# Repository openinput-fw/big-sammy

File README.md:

# big-sammy

Open source wired mouse hardware.

Please see the [documentation](https://big-sammy.readthedocs.io/en/latest) for more information.

## Specifications
- 8 kHz sampling rate support
- Zero latency switch debounce
- Onboard configuration memory
- 2 main mouse buttons (satellite* configuration for both)
- 2 side buttons (symmetric to allow easy left/right handedness)
- encoder + wheel button (satellite* configuration)
- RGB Led

`*meaning, a separate board from the core with the controller and sensor`

## Firmware

*big-sammy* is meant to run on [openinput](https://github.com/openinput-fw/openinput).

## License

This hardware is licensed under the [CERN-OHL-P v2](LICENSE) license.

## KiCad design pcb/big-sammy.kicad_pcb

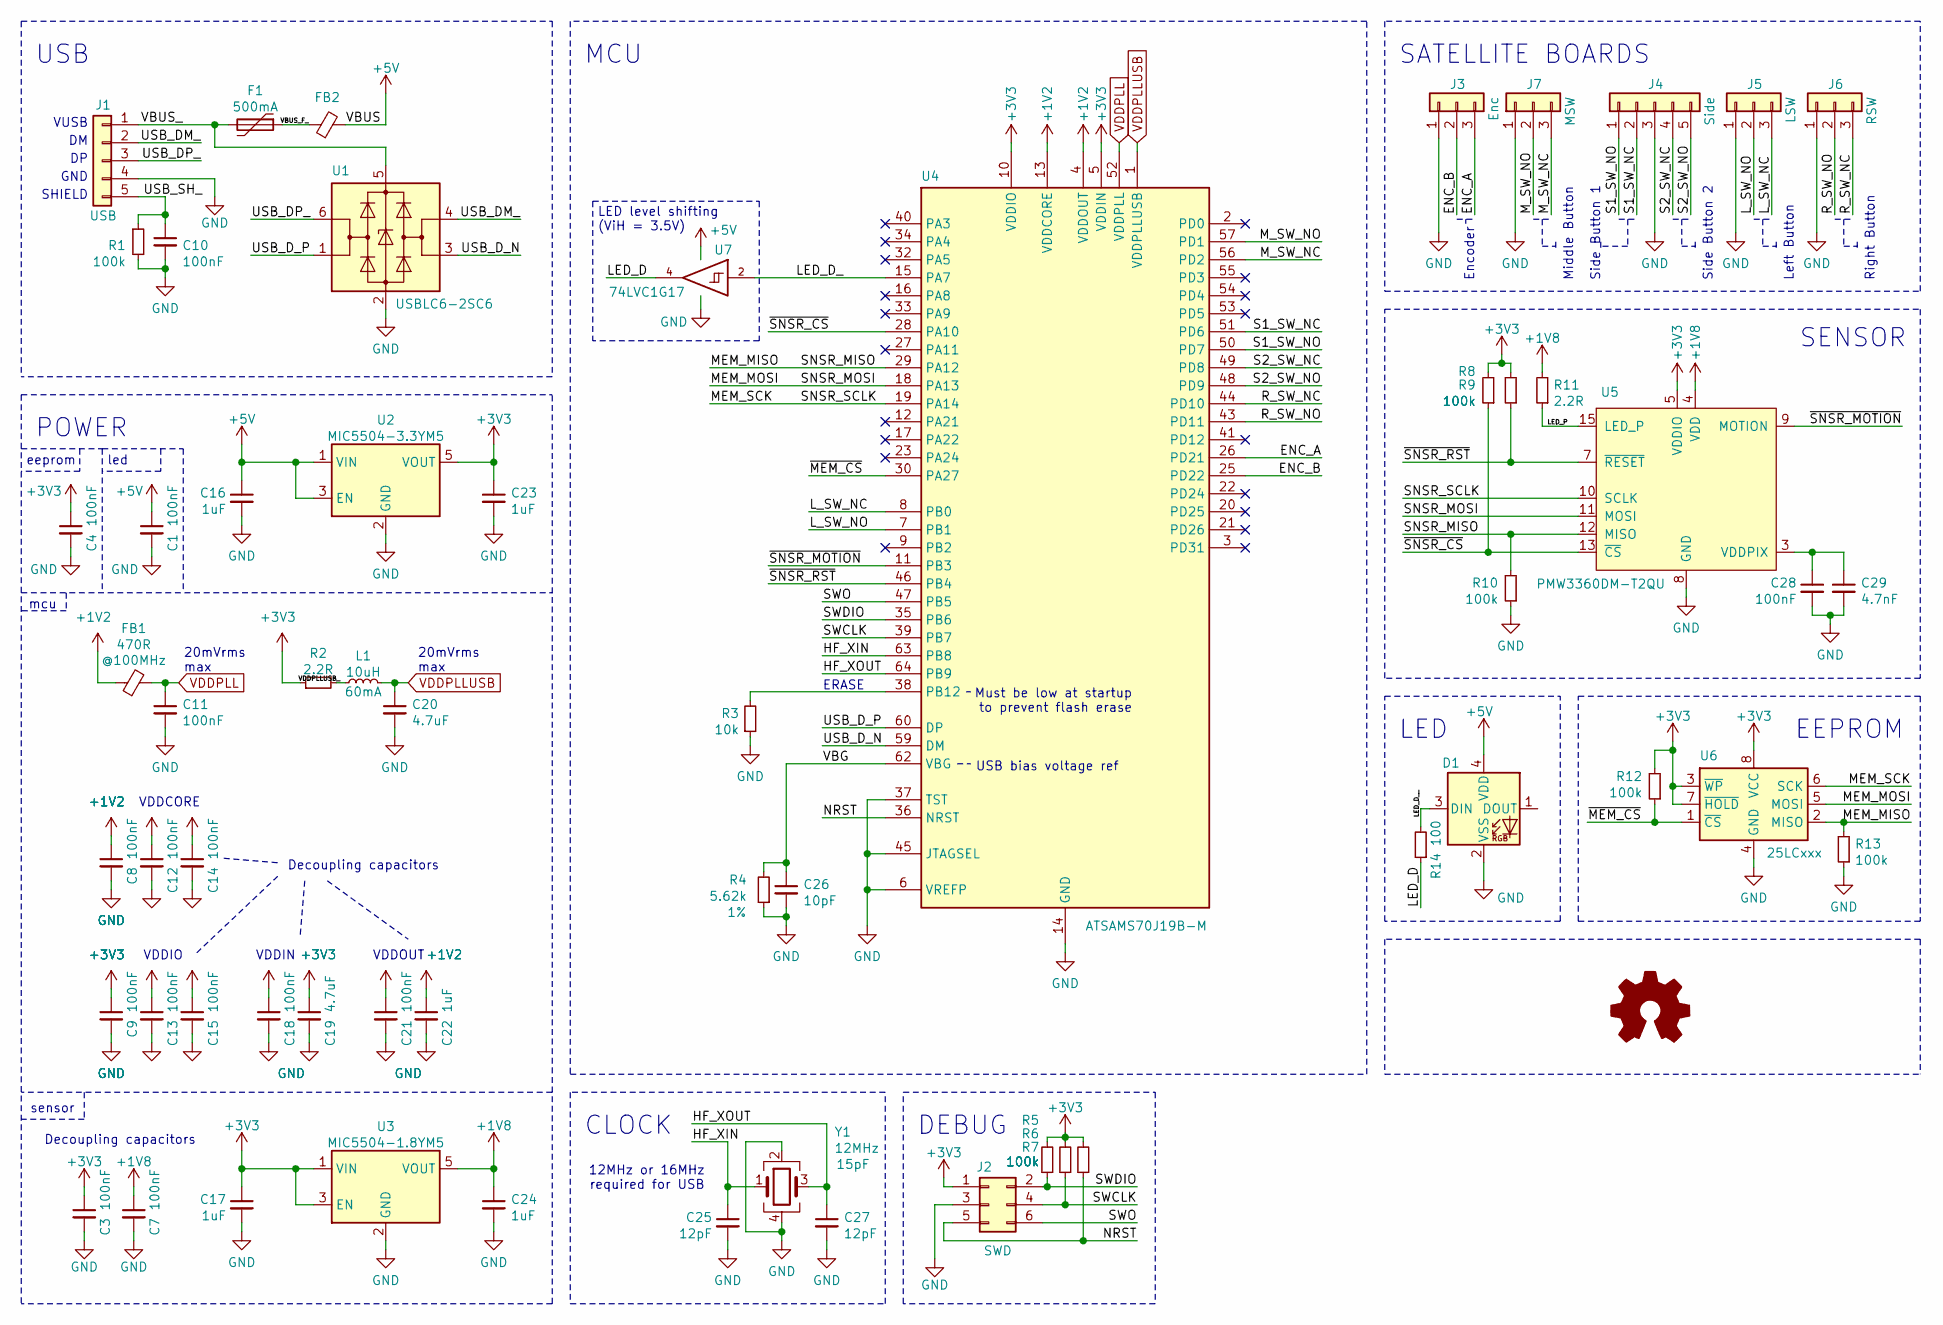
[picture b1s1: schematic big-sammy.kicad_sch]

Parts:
C1, C3, C4, C7, C8, C9, C10, C11, C12, C13, C14, C15, C18, C21, C28: 100nF; C_0402_1005Metric
C16, C17, C22, C23, C24: 1uF; C_0603_1608Metric
C19, C20: 4.7uF; C_0603_1608Metric
C25, C27: 12pF; C_0402_1005Metric
C26: 10pF; C_0402_1005Metric
C29: 4.7nF; C_0402_1005Metric
D1: ws2812-2020
F1: 500mA; Fuse_0603_1608Metric_Castellated
FB1: 470R; L_0402_1005Metric
FB2: L_0402_1005Metric
J1: USB; JST_PH_B5B-PH-K_1x05_P2.00mm_Vertical
J2: SWD; Tag-Connect_TC2030-IDC-NL_2x03_P1.27mm_Vertical
J3: Enc; JST_SH_BM03B-SRSS-TB_1x03-1MP_P1.00mm_Vertical
J4: Side; JST_SH_BM05B-SRSS-TB_1x05-1MP_P1.00mm_Vertical
J5: LSW; JST_SH_BM03B-SRSS-TB_1x03-1MP_P1.00mm_Vertical
J6: RSW; JST_SH_BM03B-SRSS-TB_1x03-1MP_P1.00mm_Vertical
J7: MSW; JST_SH_BM03B-SRSS-TB_1x03-1MP_P1.00mm_Vertical
L1: 10uH; L_0402_1005Metric
R1, R5, R6, R7, R8, R9, R10, R12, R13: 100k; R_0402_1005Metric
R2, R11: 2.2R; R_0402_1005Metric
R3: 10k; R_0402_1005Metric
R4: 5.62k; R_0402_1005Metric; Tolerance 1%
R14: 100; R_0402_1005Metric
U1: USBLC6-2SC6; SOT-23-6
U2: MIC5504-3.3YM5; SOT-23-5
U3: MIC5504-1.8YM5; SOT-23-5
U4: ATSAMS70J19B-M; QFN-64-1EP_9x9mm_P0.5mm_EP7.65x7.65mm
U5: PMW3360DM-T2QU; PMW3360
U6: 25LCxxx; DFN-S-8-1EP_6x5mm_P1.27mm
U7: 74LVC1G17; SOT-353_SC-70-5
Y1: 12MHz; Crystal_SMD_3225-4Pin_3.2x2.5mm

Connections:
+1V2: C8.1, C12.1, C14.1, C21.1, C22.1, FB1.1, U4.4 (VDDOUT), U4.13 (VDDCORE), U4.24 (VDDCORE), U4.61 (VDDCORE)
+1V8: C7.1, C24.1, R11.2, U3.5 (VOUT), U5.4 (VDD)
+3V3: C3.1, C4.1, C9.1, C13.1, C15.1, C17.1, C18.1, C19.1, C23.1, J2.1, R2.1, R5.2, R6.2, R7.2, R8.2, R9.2, R12.2, U2.5 (VOUT), U3.1 (VIN), U3.3 (EN), U4.5 (VDDIN), U4.10 (VDDIO), U4.42 (VDDIO), U4.58 (VDDIO), U5.5 (VDDIO), U6.3 (~WP), U6.7 (~HOLD), U6.8 (VCC)
+5V: C1.1, C16.1, D1.4 (VDD), FB2.2, U2.1 (VIN), U2.3 (EN), U7.5 (VCC)
/ENC_A: J3.3, U4.26 (PD21)
/ENC_B: J3.2, U4.25 (PD22)
/HF_XIN: C25.1, U4.63 (PB8), Y1.1
/HF_XOUT: C27.1, U4.64 (PB9), Y1.3
/LED_D: R14.1, U7.4
/LED_D_: U4.15 (PA7), U7.2
/LED_D__: D1.3 (DIN), R14.2
/LED_P: R11.1, U5.15 (LED_P)
/L_SW_NC: J5.3, U4.8 (PB0)
/L_SW_NO: J5.2, U4.7 (PB1)
/MEM_MISO: R10.2, R13.2, U4.29 (PA12), U5.12 (MISO), U6.2 (MISO)
/MEM_MOSI: U4.18 (PA13), U5.11 (MOSI), U6.5 (MOSI)
/MEM_SCK: U4.19 (PA14), U5.10 (SCLK), U6.6 (SCK)
/M_SW_NC: J7.3, U4.56 (PD2)
/M_SW_NO: J7.2, U4.57 (PD1)
/NRST: J2.5, R7.1, U4.36 (NRST)
/R_SW_NC: J6.3, U4.44 (PD10)
/R_SW_NO: J6.2, U4.43 (PD11)
/S1_SW_NC: J4.2, U4.51 (PD6)
/S1_SW_NO: J4.1, U4.50 (PD7)
/S2_SW_NC: J4.4, U4.49 (PD8)
/S2_SW_NO: J4.5, U4.48 (PD9)
/SWCLK: J2.4, R6.1, U4.39 (PB7)
/SWDIO: J2.2, R5.1, U4.35 (PB6)
/SWO: J2.6, U4.47 (PB5)
/USB_DM_: J1.2, U1.4 (I/O2)
/USB_DP_: J1.3, U1.6 (I/O1)
/USB_D_N: U1.3 (I/O2), U4.59 (DM)
/USB_D_P: U1.1 (I/O1), U4.60 (DP)
/USB_SH_: C10.1, J1.5, R1.1
/VBG: C26.1, R4.2, U4.62 (VBG)
/VBUS_: F1.2, J1.1, U1.5 (VBUS)
/VBUS_F_: F1.1, FB2.1
/VDDPLLUSB_: L1.1, R2.2
/~MEM_CS: R12.1, U4.30 (PA27), U6.1 (~CS)
/~SNSR_CS: R8.1, U4.28 (PA10), U5.13 (~CS)
/~SNSR_MOTION: U4.11 (PB3), U5.9 (MOTION)
/~SNSR_RST: R9.1, U4.46 (PB4), U5.7 (~RESET)
GND: C1.2, C3.2, C4.2, C7.2, C8.2, C9.2, C10.2, C11.2, C12.2, C13.2, C14.2, C15.2, C16.2, C17.2, C18.2, C19.2, C20.2, C21.2, C22.2, C23.2, C24.2, C25.2, C26.2, C27.2, C28.2, C29.2, D1.2 (VSS), J1.4, J2.3, J3.1, J4.3, J5.1, J6.1, J7.1, R1.2, R3.1, R4.1, R10.1, R13.1, U1.2 (GND), U2.2 (GND), U3.2 (GND), U4.6 (VREFP), U4.14 (GND), U4.31 (GND), U4.37 (TST), U4.45 (JTAGSEL), U4.65 (GND), U5.8 (GND), U6.4 (GND), U7.3 (GND), Y1.2, Y1.4
unnamed: C28.1, C29.1, U5.3 (VDDPIX)
unnamed: R3.2, U4.38 (PB12)
VDDPLL: C11.1, FB1.2, U4.52 (VDDPLL)
VDDPLLUSB: C20.1, L1.2, U4.1 (VDDPLLUSB)

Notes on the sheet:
Side Button 2
Left Button
DEBUG
USB
20mVrms max
CLOCK
SENSOR
USB bias voltage ref
VDDCORE
SHIELD
Right Button
VUSB
led
MCU
12MHz or 16MHz required for USB
mcu
Decoupling capacitors
Side Button 1
GND
POWER
sensor
Encoder
Middle Button
eeprom
SATELLITE BOARDS
VDDIO
LED
ERASE
LED level shifting (ViH = 3.5V)
VDDIN
Must be low at startup to prevent flash erase
EEPROM
VDDOUT

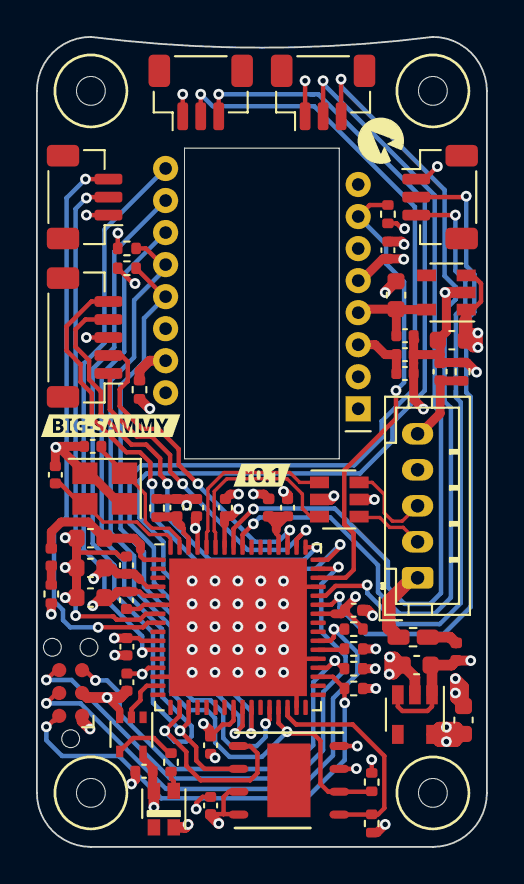
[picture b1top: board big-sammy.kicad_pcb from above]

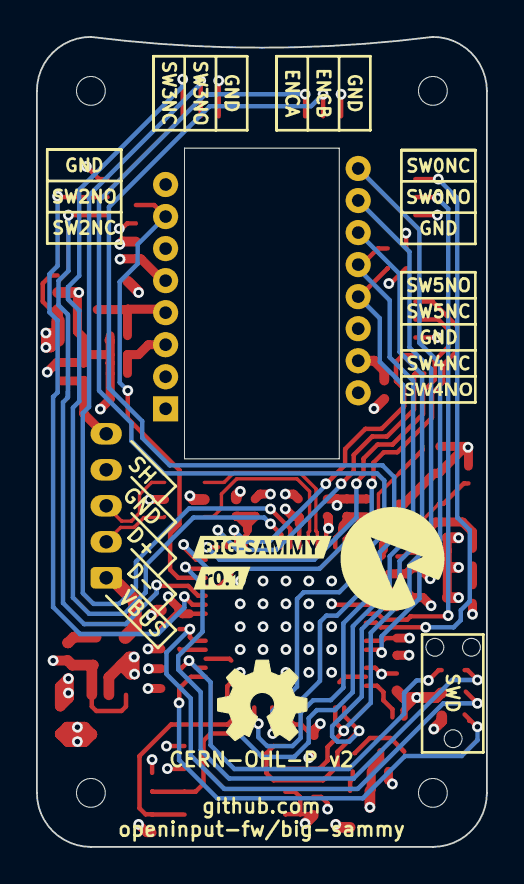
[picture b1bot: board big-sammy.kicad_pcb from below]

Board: 4 copper layers, 25.0 x 45.0 mm, 65 parts (3 on the bottom side), 47 nets.

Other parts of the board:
svg2mod, svg2mod#2, svg2mod#3, svg2mod#4, svg2mod#5: G***; svg2mod

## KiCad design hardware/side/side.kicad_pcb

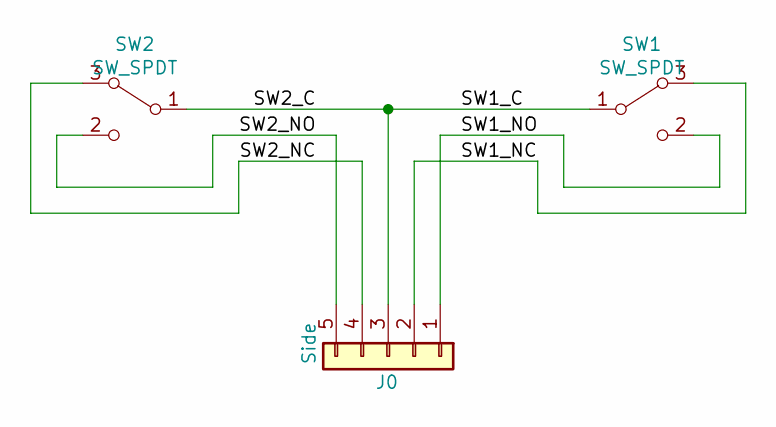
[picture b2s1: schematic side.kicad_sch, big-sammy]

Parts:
J0: Side; PinHeader_1x05_P2.00mm_Vertical
SW1, SW2: SW_SPDT; Generic

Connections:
/SW1_C: J0.3, SW1.1 (B), SW2.1 (B)
/SW1_NC: J0.2, SW1.3 (A)
/SW1_NO: J0.1, SW1.2 (C)
/SW2_NC: J0.4, SW2.3 (A)
/SW2_NO: J0.5, SW2.2 (C)

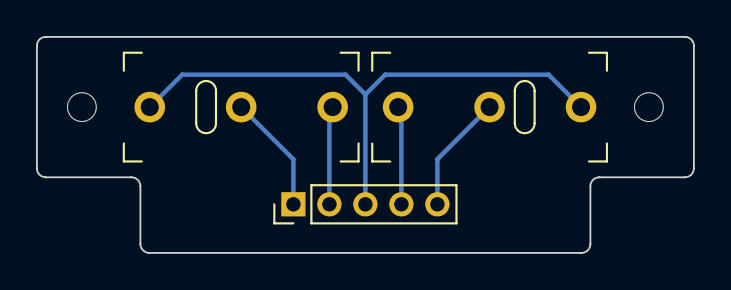
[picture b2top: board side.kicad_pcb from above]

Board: 4 copper layers, 36.5 x 12.0 mm, 3 parts (0 on the bottom side), 5 nets.

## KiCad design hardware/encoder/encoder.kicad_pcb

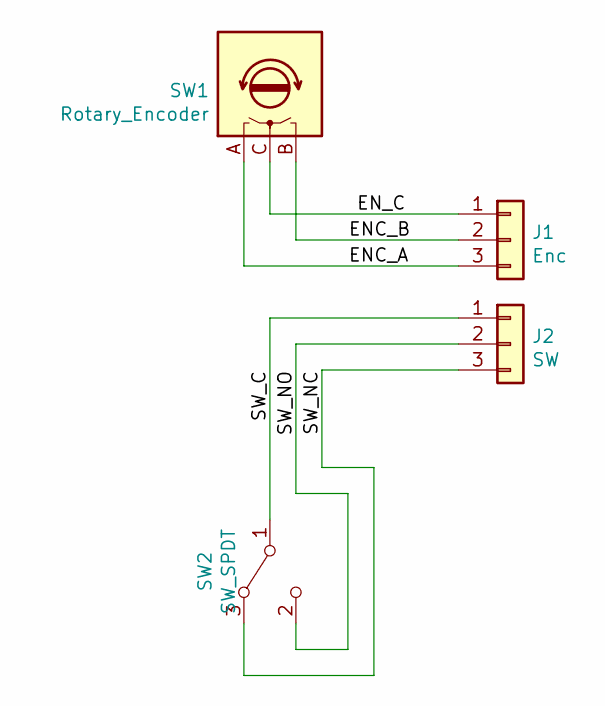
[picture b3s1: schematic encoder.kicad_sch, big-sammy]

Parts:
J1: Enc; PinHeader_1x03_P2.00mm_Vertical
J2: SW; PinHeader_1x03_P2.00mm_Vertical
SW1: Rotary_Encoder; Encoder
SW2: SW_SPDT; Generic

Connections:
/ENC_A: J1.3, SW1.A
/ENC_B: J1.2, SW1.B
/EN_C: J1.1, SW1.C
/SW_C: J2.1, SW2.1 (B)
/SW_NC: J2.3, SW2.3 (A)
/SW_NO: J2.2, SW2.2 (C)

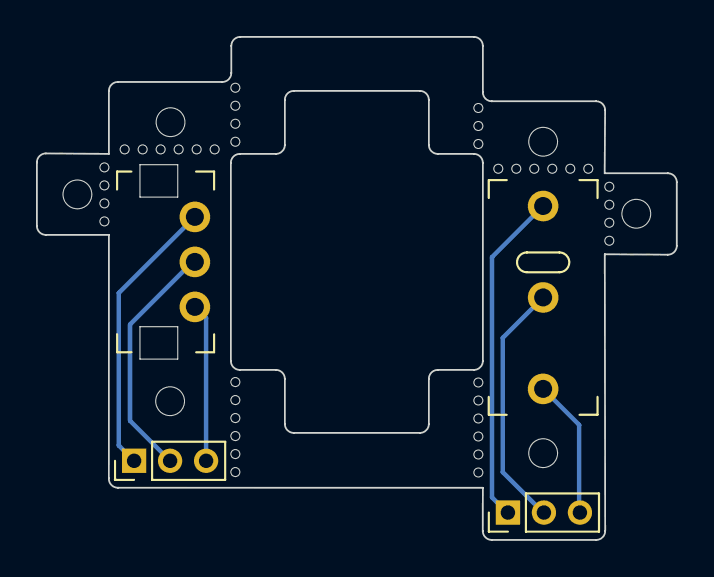
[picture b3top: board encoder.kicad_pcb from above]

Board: 4 copper layers, 35.5 x 27.9 mm, 4 parts (0 on the bottom side), 6 nets.

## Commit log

2021-04-10 license: add CERN-OHL-P v2 license
2021-04-10 readme: add readme
2021-04-10 hardware: add base projects
2021-04-10 readme: clarify mcu selection
2021-04-13 readme: add usb pinout
2021-04-13 kicad: add local libraries
2021-04-13 schematic: implement core board
2021-04-13 schematic: add current repo url
2021-04-13 git: kicad: add kicad lib backups to gitignore
2021-04-13 schematic: implement side boards
2021-04-13 schematic: add missing library table
2021-04-13 schematic: core: add rgb led
2021-04-13 schematic: core: add labels
2021-04-13 readme: add RGB Led to spec list
2021-04-13 schematic: core: fix erase pull down value (internall 100k in parallel)
2021-04-13 name: renamed project
2021-04-13 readme: mention more compatible sensors
2021-04-13 readme: add firmware section
2021-04-13 hardware: add project footprint table
2021-04-13 hardware: fix kicad table links
2021-04-13 schematic: core: changed encoder board pinout
2021-04-13 pcb: encoder: layout
2021-04-13 pcb: side: layout
2021-04-13 pcb: switch: layout
2021-04-20 pcb: core: component positioning
2021-04-21 kicad: libraries
2021-04-21 core: layout
2021-04-22 kicad: add M1.4 mounting hole
2021-04-22 core: finalize layout
2021-04-22 core: document label creation details
2021-04-22 switch: add alternative mounting points
2021-04-22 side: change mounting hardware from m2 to m1.4
2021-04-22 encoder: rework encoder board
2021-04-22 rev: bum rev to r0.1
2021-04-22 repo: update name and references to source
2021-04-22 core: pcb: fixup encoder trace
2021-04-22 readme: add r0.1 render
2021-04-22 core: pcb: fixup SW trace
2021-04-30 pcb: move kicad project, seperate generic boards from repo
2021-04-30 kicad: removed unused libs
2021-06-07 fix #1: typo in link to source
2021-07-02 readme: add peripheral board reference
2021-10-15 assets: move assets to docs/assets
2021-10-15 docs: add initial documentation with sphinx
2021-10-15 assets: oi logo cleanup
2021-10-15 docs/assets: add icon version of oi logo
2021-10-15 docs: initial index
2021-10-15 docs: add readthedocs config
2021-10-15 readme: add docs status badge
2021-10-15 docs: fix readthedocs requirements location
2021-10-15 docs: link to firmware documentation instead of source
2021-10-29 docs: doc landing page formating and improvement
2021-10-29 readme: redirect information to documentation
2021-11-05 docs: Roadmap update
2021-12-15 readme: formating
2022-01-07 kicad: save pcb with v6.0

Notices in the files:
hardware/encoder/encoder.kicad_pcb:
This source describes Open Hardware and is licensed under the CERN-OHL-Pv2
Copyright (c) Rafael Silva
